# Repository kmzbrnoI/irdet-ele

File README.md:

Infrared detector PCB
=====================

IR detector is an 8-input PCB allowing to sample signals from IR receiver
transistors. IR LED & IR fototransistor is placed near each other. This PCB
detects when signal fro emitter is received on receiver. It sends pulses to
emitter and checks for these pulses on inputs pins. Main aim of this PCB is to
smartly process signal from IR inputs so environment has no effect on inputs
states (e.g. intensity of lights).

This repository contains schematics & PCB layout of IRDET PCB. Firmware
for main MCU is available [here](https://github.com/kmzbrnoI/irdet-fw).

## Design

Schematics & PCB are designed in Eagle 9.

## Production

PCB is prepared to be automatically assembled in [JLCPCB](https://jlcpcb.com/).
SMD parts on bottom side should be assembled. Each SMD part has its `LCSC_ITEM`
attribute set.

Black silkscreen colour is advised.

## Parameters

 * Input voltage: 7–17 V.
   Protection: when > 18 V is applied, input is shorted. Afterwards, current
   is limited by PTC fuse on input to 200 mA. Changed-polarity protection.
 * Max current consumption: 150 mA.
 * Inputs: up to 8 IRs. Any number of IRs can be connected. Pulled up to +5 V
   internally. Capacitive coupling is used on inputs. No over-voltage protection.
 * IR LEDs: driver for each pair of IR LEDs. Short peaks of 100 mA stable current.
 * Logic outputs: galvanically separated from rest of PCB.

## Authors

The module is designed by Jan Horáček,
[Model Railway Club Brno](https://www.kmz-brno.cz/).

## License

Content of the repository is provided under [Creative Commons
Attribution-ShareAlike 4.0
License](https://creativecommons.org/licenses/by-sa/4.0/) as openhardware
project. You may download any data, contribute to the project, create PCB
yourself or even sell it yourself.

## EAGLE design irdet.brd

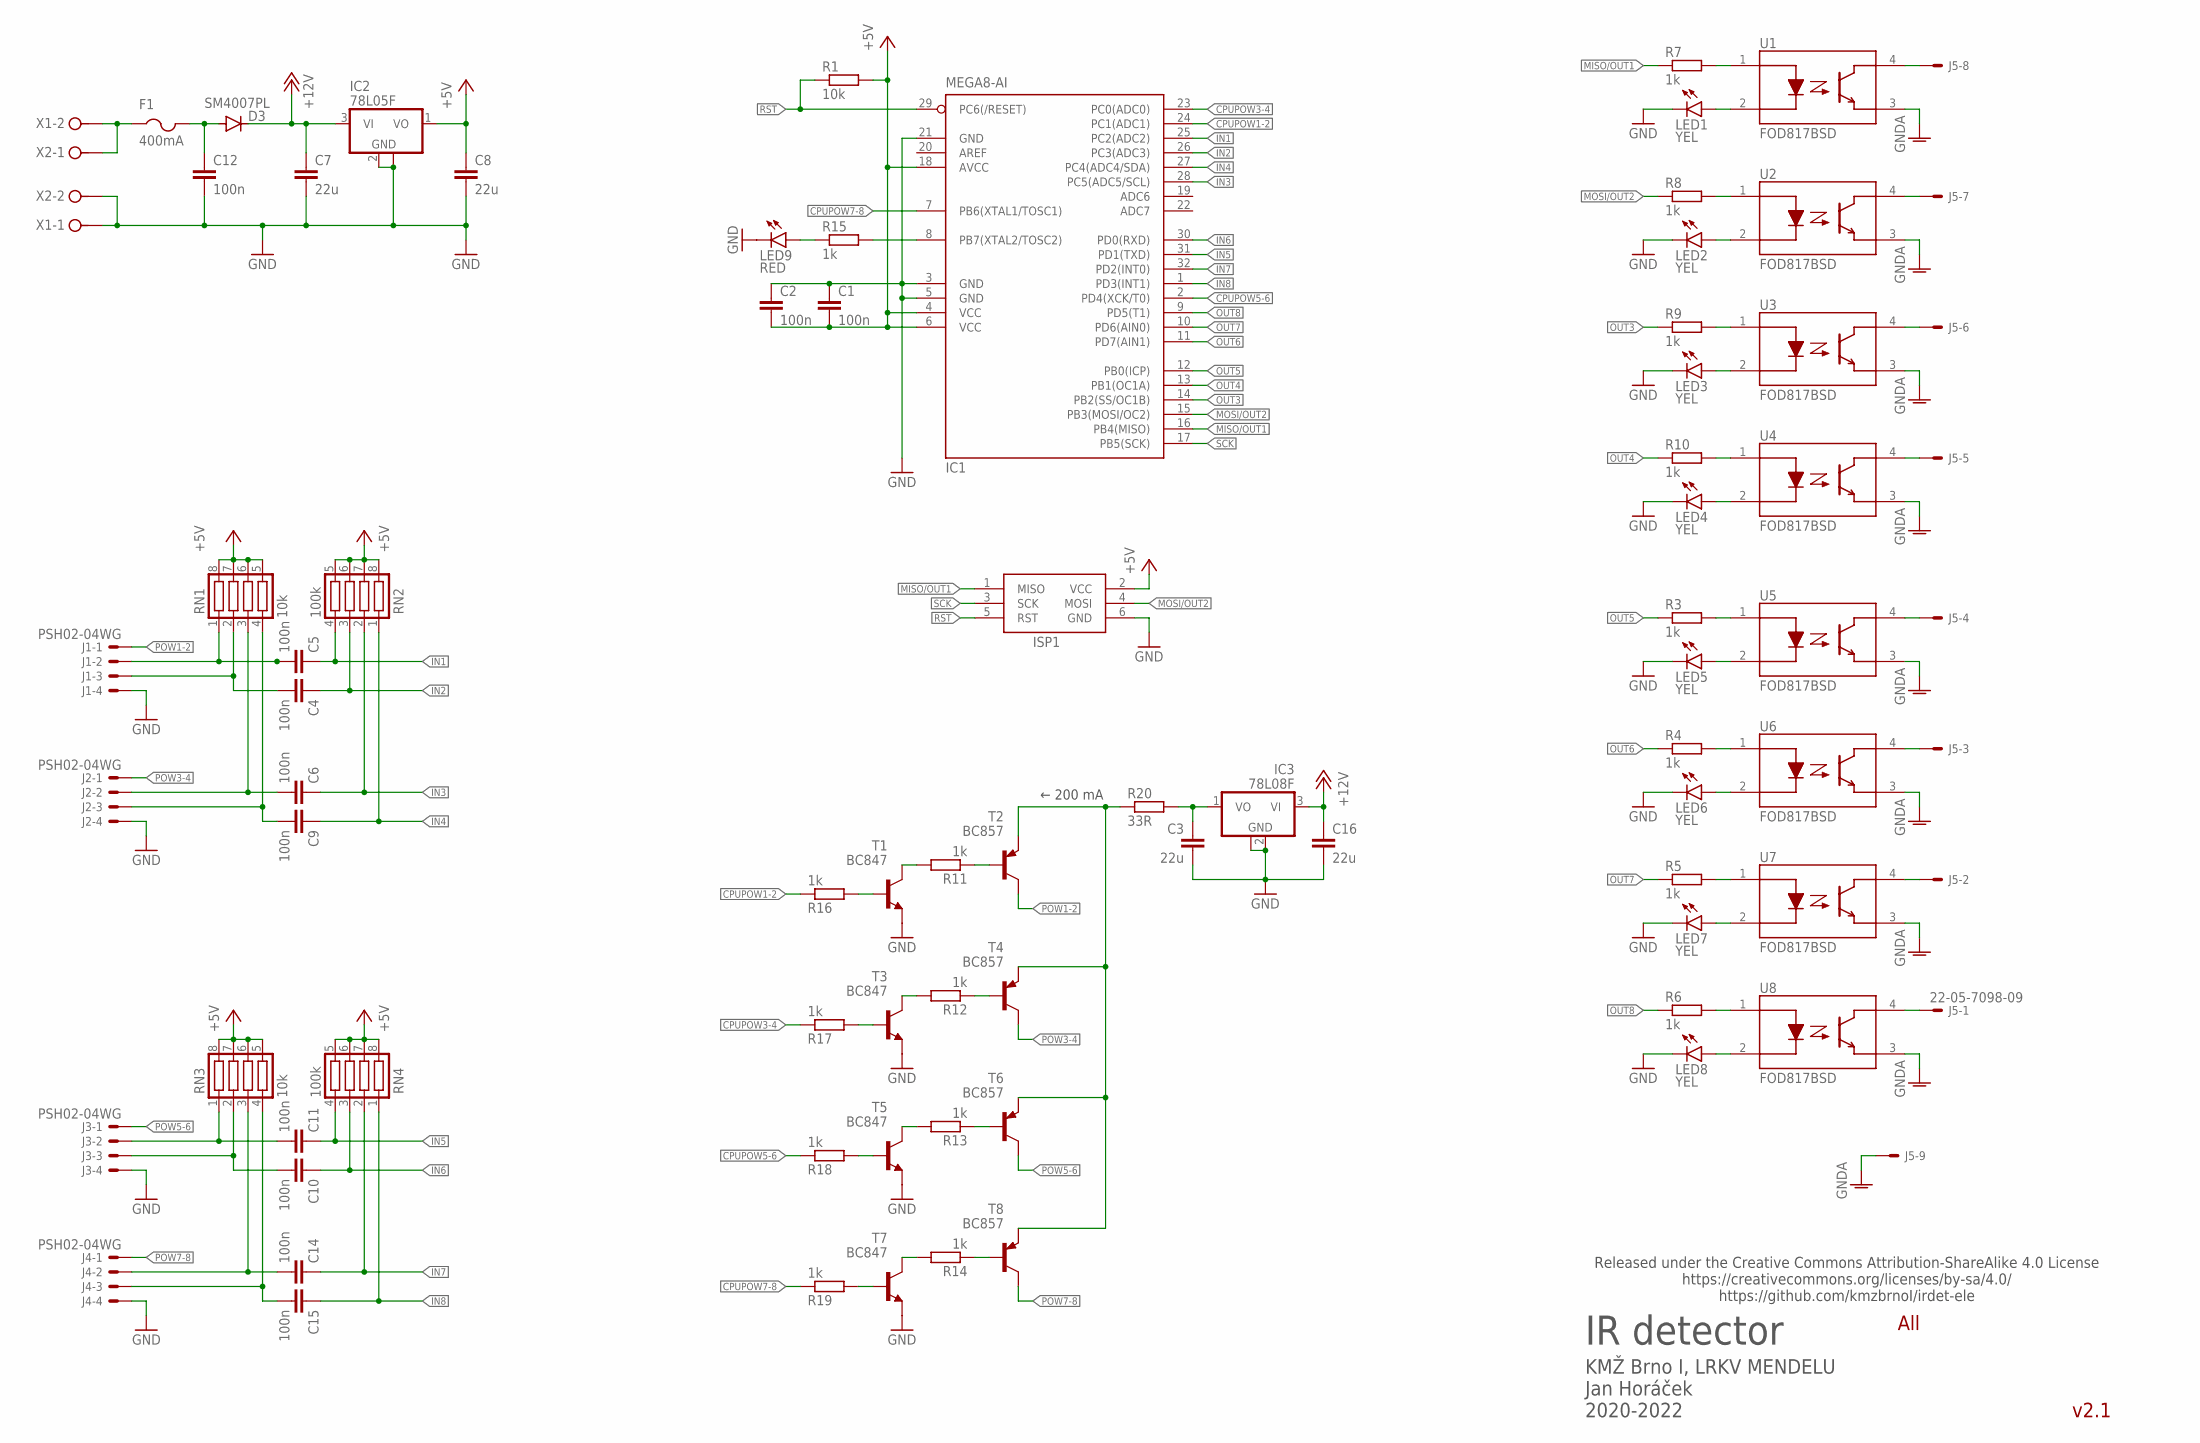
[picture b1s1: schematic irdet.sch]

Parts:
C1, C2, C4, C5, C6, C9, C10, C11, C14, C15: 100n; C0805; LCSC_PART C49678
C3, C7, C8, C16: 22u; C0805; LCSC_PART C45783
C12: 100n; C0805; LCSC_PART C49478
D3: SM4007PL; SOD-123_MINI-SMA; LCSC_PART C64898
F1: 400mA; R0805
IC1: MEGA8-AI; TQFP32-08; LCSC_PART C16190
IC2: 78L05F; SOT89; LCSC_PART C71136
IC3: 78L08F; SOT89; LCSC_PART C122846
ISP1: AVRISP-6; AVRISP
J1, J2, J3, J4: PSH02-04WG; 7395-04
J5: 22-05-7098-09; 7395-09
LED1, LED2, LED3, LED4, LED5, LED6, LED7, LED8: YEL; CHIPLED_0805
LED9: RED; CHIPLED_0805
R1: 10k; R0805; LCSC_PART C17414
R3, R4, R5, R6, R7, R8, R9, R10, R11, R12, R13, R14, R15, R16, R17, R18, R19: 1k; R0805; LCSC_PART C17513
R20: 33R; R2010
RN1, RN3: 10k; CTS742C083; LCSC_PART C29718
RN2, RN4: 100k; CTS742C083; LCSC_PART C173315
T1, T3, T5, T7: BC847; SOT23-BEC
T2, T4, T6, T8: BC857; SOT23-BEC
U1, U2, U3, U4, U5, U6, U7, U8: FOD817BSD; LCSC_PART C106900
X1, X2: MVE252-5-V

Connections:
+5V: C1.2, C2.2, C8.1, IC1.4 (VCC), IC1.6 (VCC), IC1.18 (AVCC), IC2.1 (VO), ISP1.2 (VCC), R1.2, RN1.5, RN1.6, RN1.7, RN1.8, RN2.5, RN2.6, RN2.7, RN2.8, RN3.5, RN3.6, RN3.7, RN3.8, RN4.5, RN4.6, RN4.7, RN4.8
+8V: C3.1, IC3.1 (VO), R20.2
+12V: C7.1, C16.1, D3.C, IC2.3 (VI), IC3.3 (VI)
+12VIN: F1.1, X1.2, X2.1
CPUPOW1-2: IC1.24 (PC1(ADC1)), R16.1
CPUPOW3-4: IC1.23 (PC0(ADC0)), R17.1
CPUPOW5-6: IC1.2 (PD4(XCK/T0)), R18.1
CPUPOW7-8: IC1.7 (PB6(XTAL1/TOSC1)), R19.1
GND: C1.1, C2.1, C3.2, C7.2, C8.2, C12.2, C16.2, IC1.3 (GND), IC1.5 (GND), IC1.21 (GND), IC2.2 (GND), IC2.2@1 (GND), IC3.2 (GND), IC3.2@1 (GND), ISP1.6 (GND), J1.4, J2.4, J3.4, J4.4, LED1.C, LED2.C, LED3.C, LED4.C, LED5.C, LED6.C, LED7.C, LED8.C, LED9.C, T1.E, T3.E, T5.E, T7.E, X1.1, X2.2
GNDA: J5.9, U1.3 (EMITTER), U2.3 (EMITTER), U3.3 (EMITTER), U4.3 (EMITTER), U5.3 (EMITTER), U6.3 (EMITTER), U7.3 (EMITTER), U8.3 (EMITTER)
IN1: C5.1, IC1.25 (PC2(ADC2)), RN2.4
IN2: C4.1, IC1.26 (PC3(ADC3)), RN2.3
IN3: C6.1, IC1.28 (PC5(ADC5/SCL)), RN2.2
IN4: C9.1, IC1.27 (PC4(ADC4/SDA)), RN2.1
IN5: C11.1, IC1.31 (PD1(TXD)), RN4.4
IN6: C10.1, IC1.30 (PD0(RXD)), RN4.3
IN7: C14.1, IC1.32 (PD2(INT0)), RN4.2
IN8: C15.1, IC1.1 (PD3(INT1)), RN4.1
MISO/OUT1: IC1.16 (PB4(MISO)), ISP1.1 (MISO), R7.1
MOSI/OUT2: IC1.15 (PB3(MOSI/OC2)), ISP1.4 (MOSI), R8.1
unnamed: C5.2, J1.2, RN1.1
unnamed: C4.2, J1.3, RN1.2
unnamed: C11.2, J3.2, RN3.1
unnamed: C10.2, J3.3, RN3.2
unnamed: C6.2, J2.2, RN1.3
unnamed: C9.2, J2.3, RN1.4
unnamed: C14.2, J4.2, RN3.3
unnamed: C15.2, J4.3, RN3.4
unnamed: LED5.A, U5.2 (CATHODE)
unnamed: R3.2, U5.1 (ANODE)
unnamed: R6.2, U8.1 (ANODE)
unnamed: R5.2, U7.1 (ANODE)
unnamed: R11.1, T2.B
unnamed: R4.2, U6.1 (ANODE)
unnamed: LED6.A, U6.2 (CATHODE)
unnamed: LED7.A, U7.2 (CATHODE)
unnamed: LED8.A, U8.2 (CATHODE)
unnamed: LED1.A, U1.2 (CATHODE)
unnamed: R7.2, U1.1 (ANODE)
unnamed: R10.2, U4.1 (ANODE)
unnamed: R9.2, U3.1 (ANODE)
unnamed: R8.2, U2.1 (ANODE)
unnamed: LED2.A, U2.2 (CATHODE)
unnamed: LED3.A, U3.2 (CATHODE)
unnamed: LED4.A, U4.2 (CATHODE)
unnamed: J5.1, U8.4 (COLLECTOR)
unnamed: J5.2, U7.4 (COLLECTOR)
unnamed: J5.3, U6.4 (COLLECTOR)
unnamed: J5.4, U5.4 (COLLECTOR)
unnamed: J5.7, U2.4 (COLLECTOR)
unnamed: J5.8, U1.4 (COLLECTOR)
unnamed: J5.6, U3.4 (COLLECTOR)
unnamed: J5.5, U4.4 (COLLECTOR)
unnamed: IC1.8 (PB7(XTAL2/TOSC2)), R15.2
unnamed: R11.2, T1.C
unnamed: R12.1, T4.B
unnamed: R12.2, T3.C
unnamed: R13.1, T6.B
unnamed: R13.2, T5.C
unnamed: R14.1, T8.B
unnamed: R14.2, T7.C
unnamed: R20.1, T2.E, T4.E, T6.E, T8.E
unnamed: LED9.A, R15.1
unnamed: R17.2, T3.B
unnamed: R16.2, T1.B
unnamed: R18.2, T5.B
unnamed: R19.2, T7.B
unnamed: C12.1, D3.A, F1.2
OUT3: IC1.14 (PB2(SS/OC1B)), R9.1
OUT4: IC1.13 (PB1(OC1A)), R10.1
OUT5: IC1.12 (PB0(ICP)), R3.1
OUT6: IC1.11 (PD7(AIN1)), R4.1
OUT7: IC1.10 (PD6(AIN0)), R5.1
OUT8: IC1.9 (PD5(T1)), R6.1
POW1-2: J1.1, T2.C
POW3-4: J2.1, T4.C
POW5-6: J3.1, T6.C
POW7-8: J4.1, T8.C
RST: IC1.29 (PC6(/RESET)), ISP1.5 (RST), R1.1
SCK: IC1.17 (PB5(SCK)), ISP1.3 (SCK)

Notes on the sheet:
IR detector
v2.1
KMŽ Brno I, LRKV MENDELU Jan Horáček 2020-2022
Released under the Creative Commons Attribution-ShareAlike 4.0 License https://creativecommons.org/licenses/by-sa/4.0/ https://github.com/kmzbrnoI/irdet-ele
All
← 200 mA

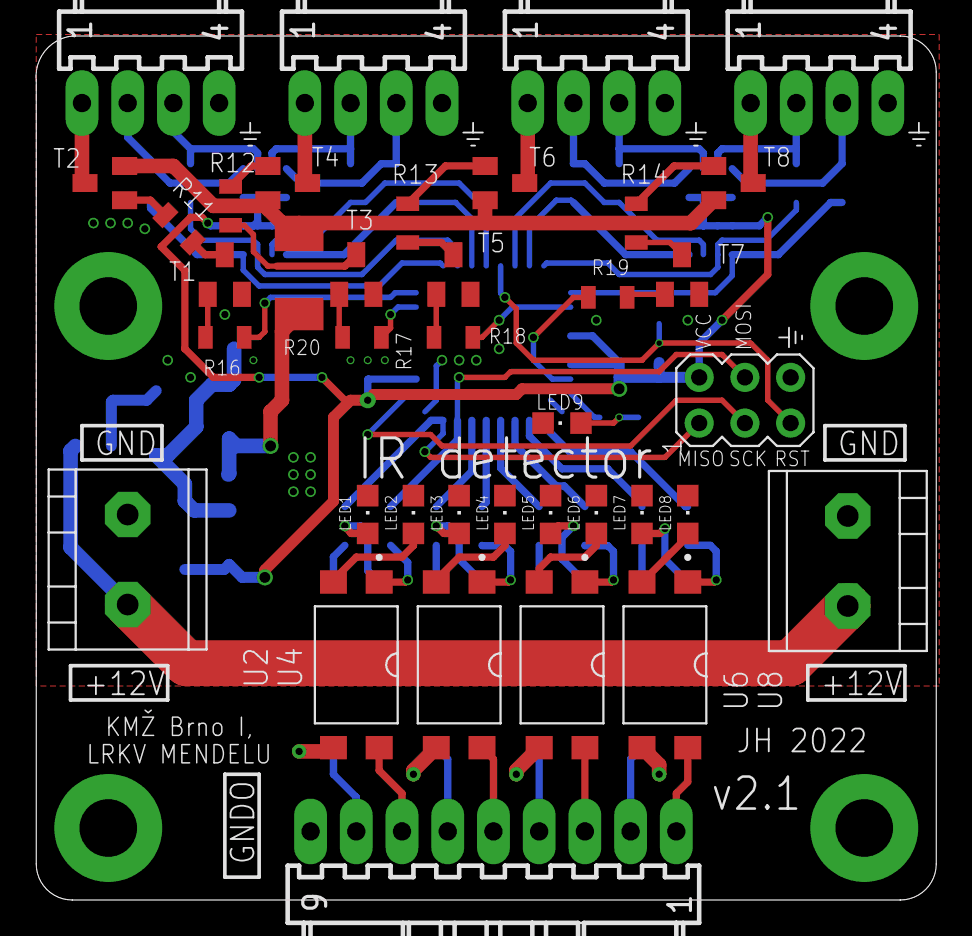
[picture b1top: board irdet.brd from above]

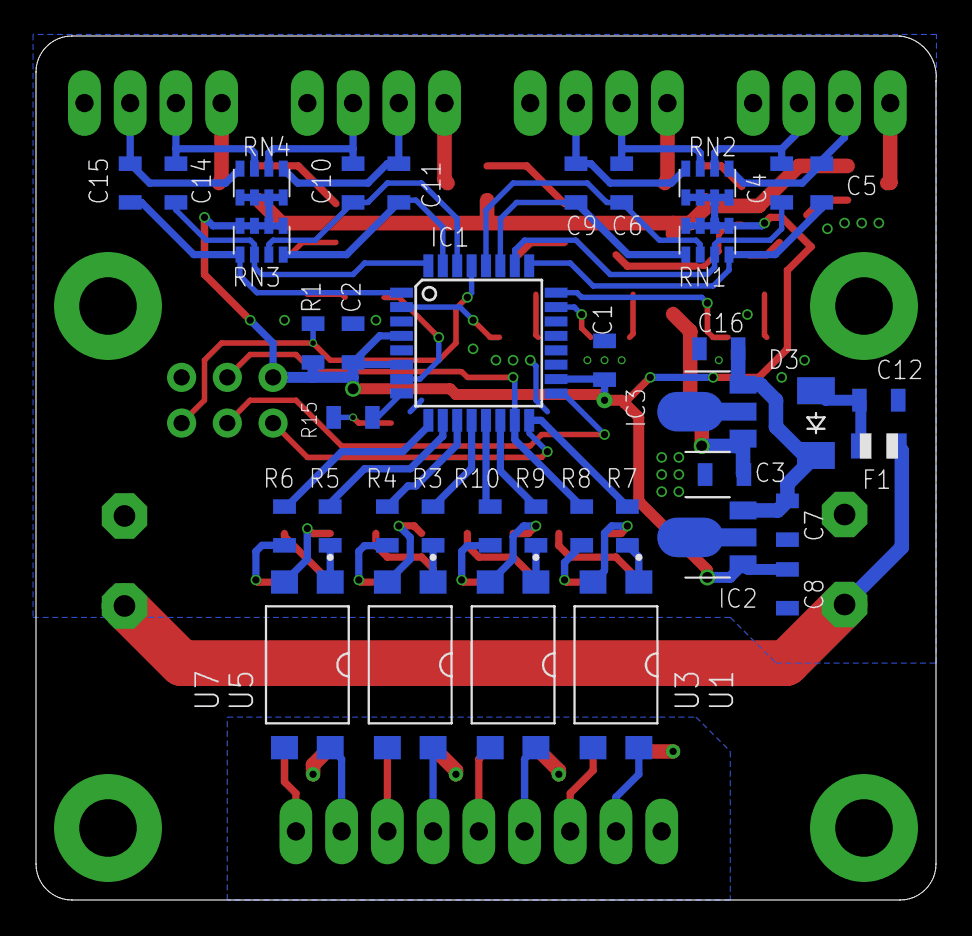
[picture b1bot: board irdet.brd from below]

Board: 2 copper layers, 50.0 x 48.0 mm, 76 parts (38 on the bottom side), 80 nets.

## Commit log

2020-12-14 Add .gitignore.
2020-12-14 Add README.
2020-12-14 Add schematics.
2020-12-14 Add cpu & stabilization.
2020-12-14 Add inputs, connect MCU.
2020-12-14 Add IR diodes powering.
2020-12-14 Move symbols in schematics.
2020-12-14 IOPOW → CPUPOW.
2020-12-14 Add capacitor to IR power generator.
2020-12-15 Do not use ADC-only inputs of CPU.
2020-12-15 Fix wire name.
2020-12-16 Add board.
2020-12-16 Rotate CPU.
2020-12-16 Add rest of PCB.
2020-12-16 Brd: add texts, position names on silkscreen.
2020-12-16 Fix parts names.
2020-12-17 Brd: add round corners.
2020-12-17 Brd: fix DRC errors & warnings.
2020-12-17 Place values.
2021-01-23 Move 22u capacitors to bottom layer.
    So all the capacitors could be soldered automatically.
2021-01-24 TLP290 → TLP292.
2021-01-28 Use proper connectors (MVE252-5-V).
2021-02-04 Add LCSC numbers to parts.
2021-02-06 Add CC license.
2021-02-06 Advice sislkscreen colour.
2021-03-01 Change transistors to more common.
2021-03-04 Fix bad part value.
2021-03-08 Fix shortcut on PCB.
2021-03-09 Change pull-up input resistors to 100k.
2021-03-09 Move ground symbols nearer to pins.
2021-03-09 Fix ERC issues.
2021-03-09 Add status LED.
2021-03-10 Add resistors to transistor's base.
2021-03-10 Update IR diode power.
    * Add stabilizer to 8V + big resistor for current ~200 mA.
    * Remove overvoltage protection.
2021-03-10 Minor tweaks.
2021-03-10 Change version to 2.0.
2021-03-10 Make silkscreen nice.
2021-03-10 Minimize drills to avoid interconnection.
2021-03-10 Change IR resistor to 33R (~200 mA).
2021-03-13 Fix part description placement.
2021-03-25 Cover vias with soldermask.
2022-06-30 Use EL817 optocouplers instead of expensive TLP292.
2022-07-02 Remove wire stub (DRC ok).
2022-07-02 Fix 100n capacitors LCSC_PART.
2022-08-19 Make part place nice.
